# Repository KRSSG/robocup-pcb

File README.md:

# RoboCup PCB Repository

Welcome to the KRRSG's repository for management and storage of RoboCup SSL hardware files! Additional information about the team can be found on the [KRSSG Website](http://www.krssg.in).

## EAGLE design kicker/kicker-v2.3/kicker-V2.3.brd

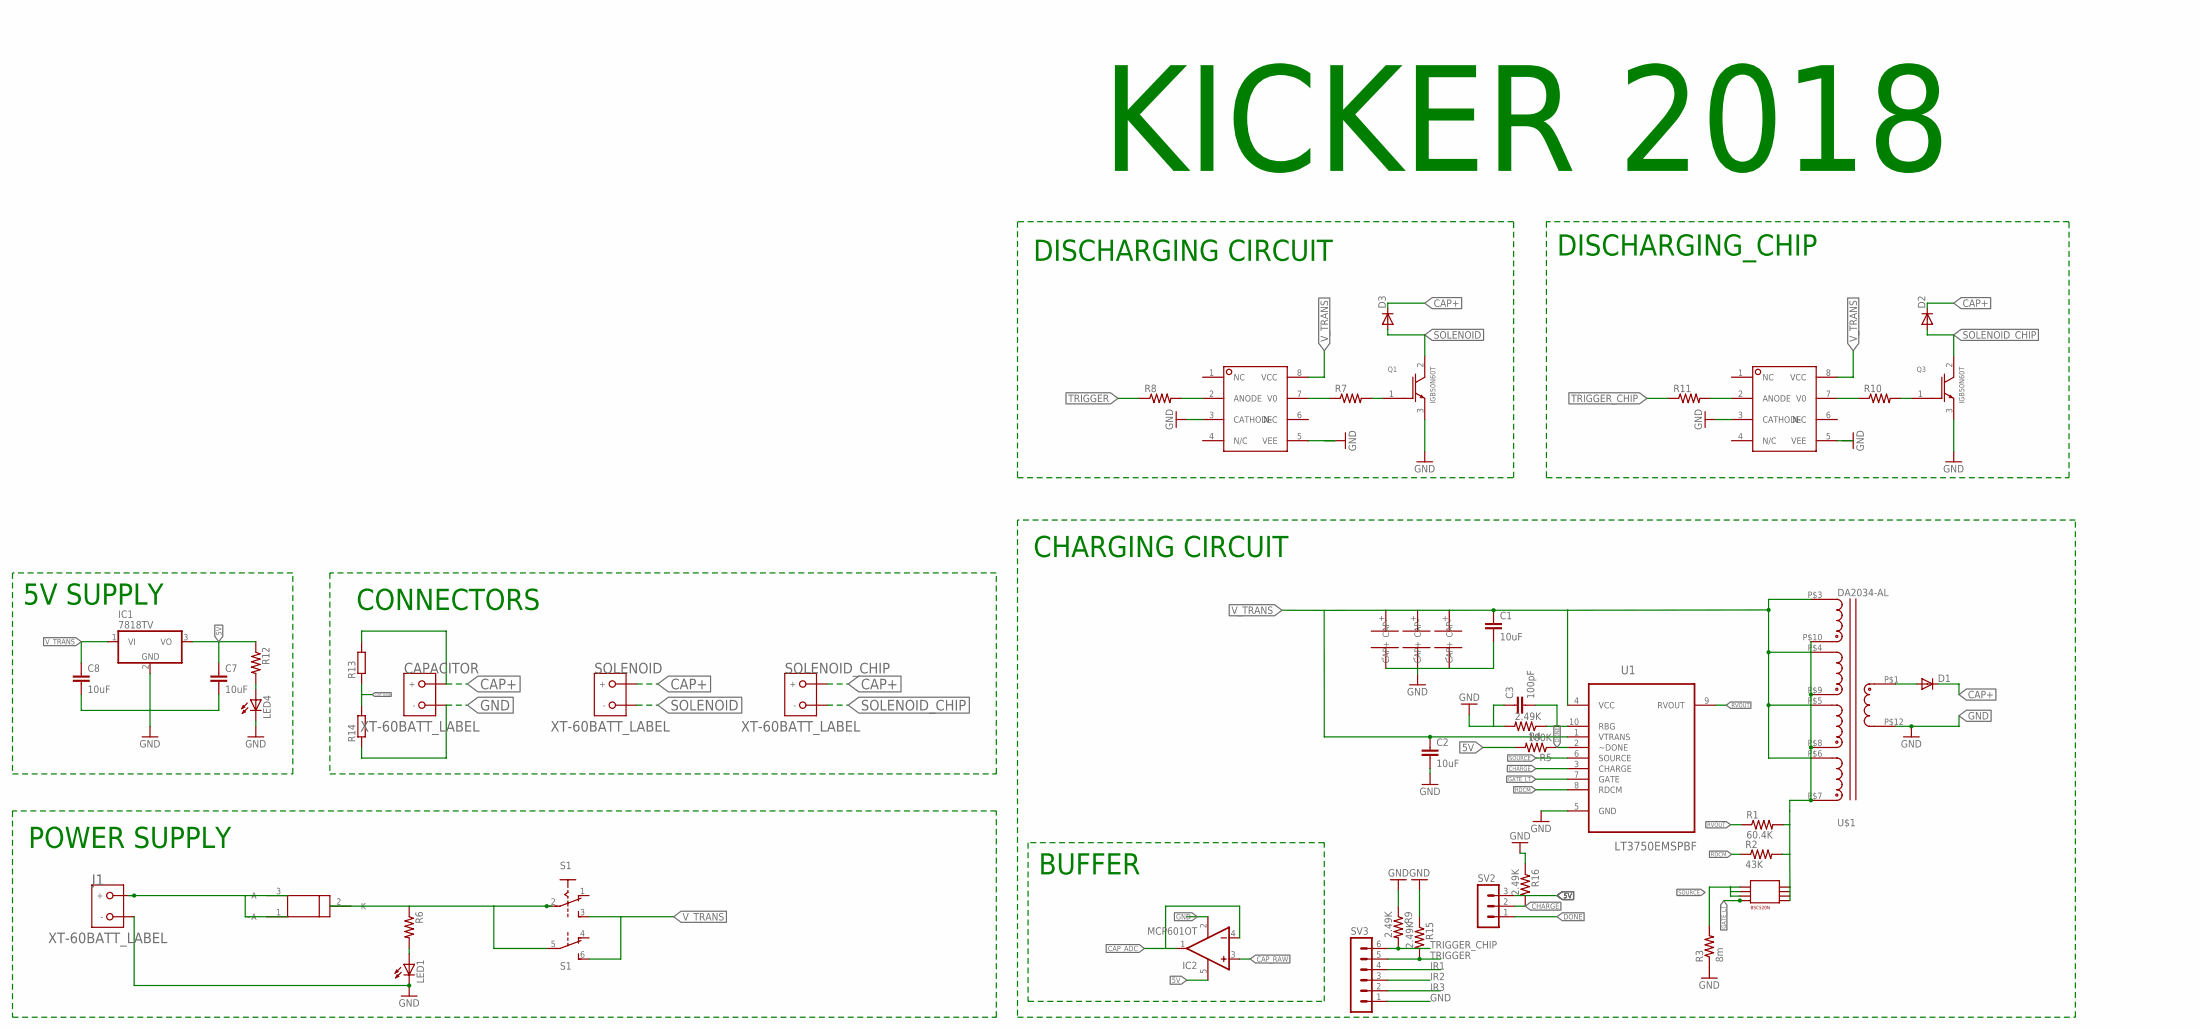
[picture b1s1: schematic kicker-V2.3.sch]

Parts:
C1, C2, C7, C8: 10uF; C1206
C3: 100pF; C1206
CAPACITOR: XT-60BATT_LABEL; XT-60
D1, D2, D3: DIODE-DO214AA; DO214AA
IC1: 7818TV; TO220V
IC2: MCP601OT; SOT23-5
J1: XT-60BATT_LABEL; XT-60
LED1, LED4: LEDCHIPLED_1206; CHIPLED_1206
Q1, Q3: IGB50N60T; TO254P1524X457-3N-2-V
R1: 60.4K; M1206
R2: 43K; M1206
R3: 8m; M1206
R4, R9, R15, R16: 2.49K; M1206
R5: 100K; M1206
R6, R7, R8, R10, R11, R12: R-US_M1206; M1206
R13, R14: R-EU_R0805; R0805
S1: A68-A31
SOLENOID: XT-60BATT_LABEL; XT-60
SOLENOID_CHIP: XT-60BATT_LABEL; XT-60
SV2: MA03-1
SV3: MA06-1
U1: LT3750EMSPBF; SOP50P490X110-10N
U3: LP38690DT-3.3; TO228P1042X238-3N
U$1: DA2034-AL
U$2, U$3, U$4: 56uF; SVP_F12
U$5: BSC520N; PG-TDSON-8
U$6, U$7: HCPL-3120-300E; DIL08

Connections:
5V: C7.1, IC1.3 (VO), IC2.5 (V+), R5.2, R12.1, SV2.3
CAP+: CAPACITOR.BATT (+), D1.C, D2.C, D3.C, R13.2, SOLENOID.BATT (+), SOLENOID_CHIP.BATT (+)
CAP_ADC: IC2.1 (OUT), IC2.4 (-IN)
CAP_RAW: IC2.3 (+IN), R13.1, R14.2
CHARGE: R16.2, SV2.2, U1.3 (CHARGE)
DONE: R5.1, SV2.1, U1.2 (~DONE)
GATE_LT: U1.7 (GATE), U$5.G
GND: C1.2, C2.2, C3.1, C7.2, C8.2, CAPACITOR.GND (-), IC1.2 (GND), IC2.2 (V-), J1.GND (-), LED1.C, LED4.C, Q1.3 (EMITTER), Q3.3 (EMITTER), R3.1, R4.2, R9.1, R14.1, R15.1, R16.1, SV3.1, U1.5 (GND), U$1.P$12 (12), U$2.- (CAP-), U$3.- (CAP-), U$4.- (CAP-), U$6.3 (CATHODE), U$6.5 (VEE), U$7.3 (CATHODE), U$7.5 (VEE)
IR1: SV3.4
IR2: SV3.3
IR3: SV3.2
unnamed: R7.1, U$6.7 (V0)
unnamed: C3.2, R4.1, U1.10 (RBG)
unnamed: R6.1, S1.2, S1.5, U3.2 (K)
unnamed: Q1.1 (GATE), R7.2
unnamed: R8.2, U$6.2 (ANODE)
unnamed: D1.A, U$1.P$1 (1)
unnamed: LED1.A, R6.2
unnamed: R10.1, U$7.7 (V0)
unnamed: Q3.1 (GATE), R10.2
unnamed: R11.2, U$7.2 (ANODE)
unnamed: LED4.A, R12.2
RDCM: R2.1, U1.8 (RDCM)
RVOUT: R1.1, U1.9 (RVOUT)
SINK: R1.2, R2.2, U$1.P$7 (7), U$1.P$8 (8), U$1.P$9 (9), U$1.P$10 (10), U$5.D1, U$5.D2, U$5.D3, U$5.D4
SOLENOID: D3.A, Q1.2 (COLLECTOR), SOLENOID.GND (-)
SOLENOID_CHIP: D2.A, Q3.2 (COLLECTOR), SOLENOID_CHIP.GND (-)
SOURCE: R3.2, U1.6 (SOURCE), U$5.S1, U$5.S2, U$5.S3
TRIGGER: R8.1, R15.2, SV3.5
TRIGGER_CHIP: R9.2, R11.1, SV3.6
VIN: J1.BATT (+), U3.1 (~A), U3.3 (A)
V_TRANS: C1.1, C2.1, C8.1, IC1.1 (VI), S1.3 (S), S1.6 (S), U1.1 (VTRANS), U1.4 (VCC), U$1.P$3 (3), U$1.P$4 (4), U$1.P$5 (5), U$1.P$6 (6), U$2.+ (CAP+), U$3.+ (CAP+), U$4.+ (CAP+), U$6.8 (VCC), U$7.8 (VCC)

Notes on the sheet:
DISCHARGING CIRCUIT
POWER SUPPLY
CHARGING CIRCUIT
DISCHARGING_CHIP
5V SUPPLY
CONNECTORS
KICKER 2018
BUFFER

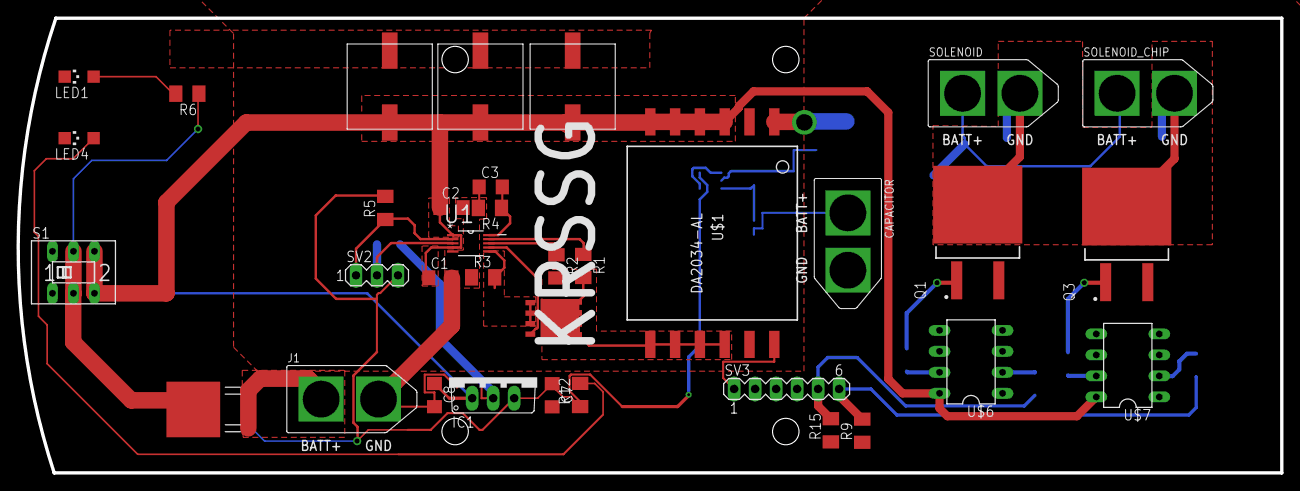
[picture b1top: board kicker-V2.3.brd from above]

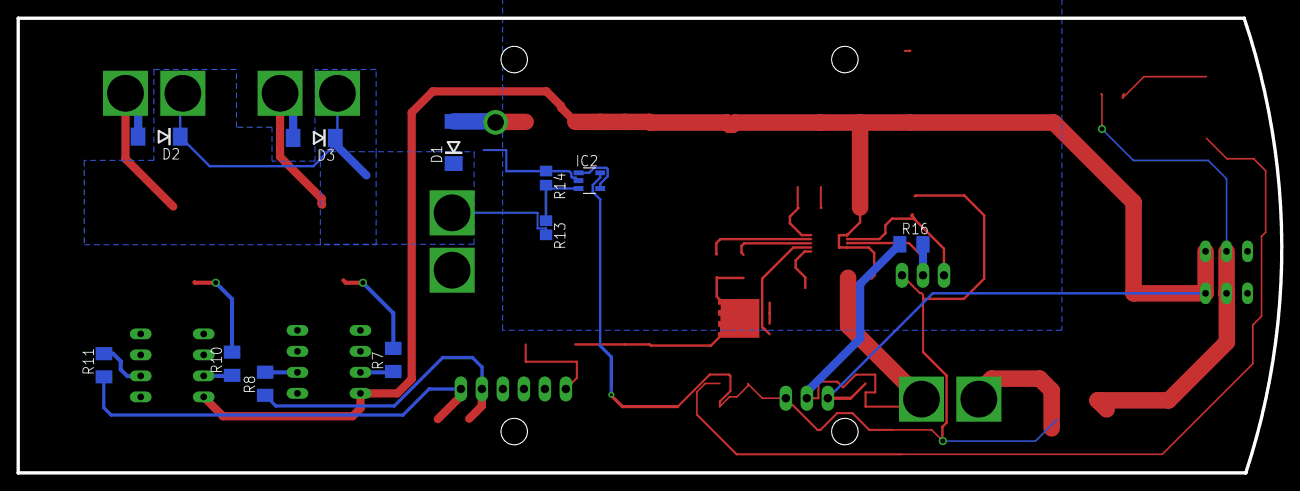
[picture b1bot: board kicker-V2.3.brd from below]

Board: 2 copper layers, 152.9 x 55.0 mm, 46 parts (11 on the bottom side), 29 nets.

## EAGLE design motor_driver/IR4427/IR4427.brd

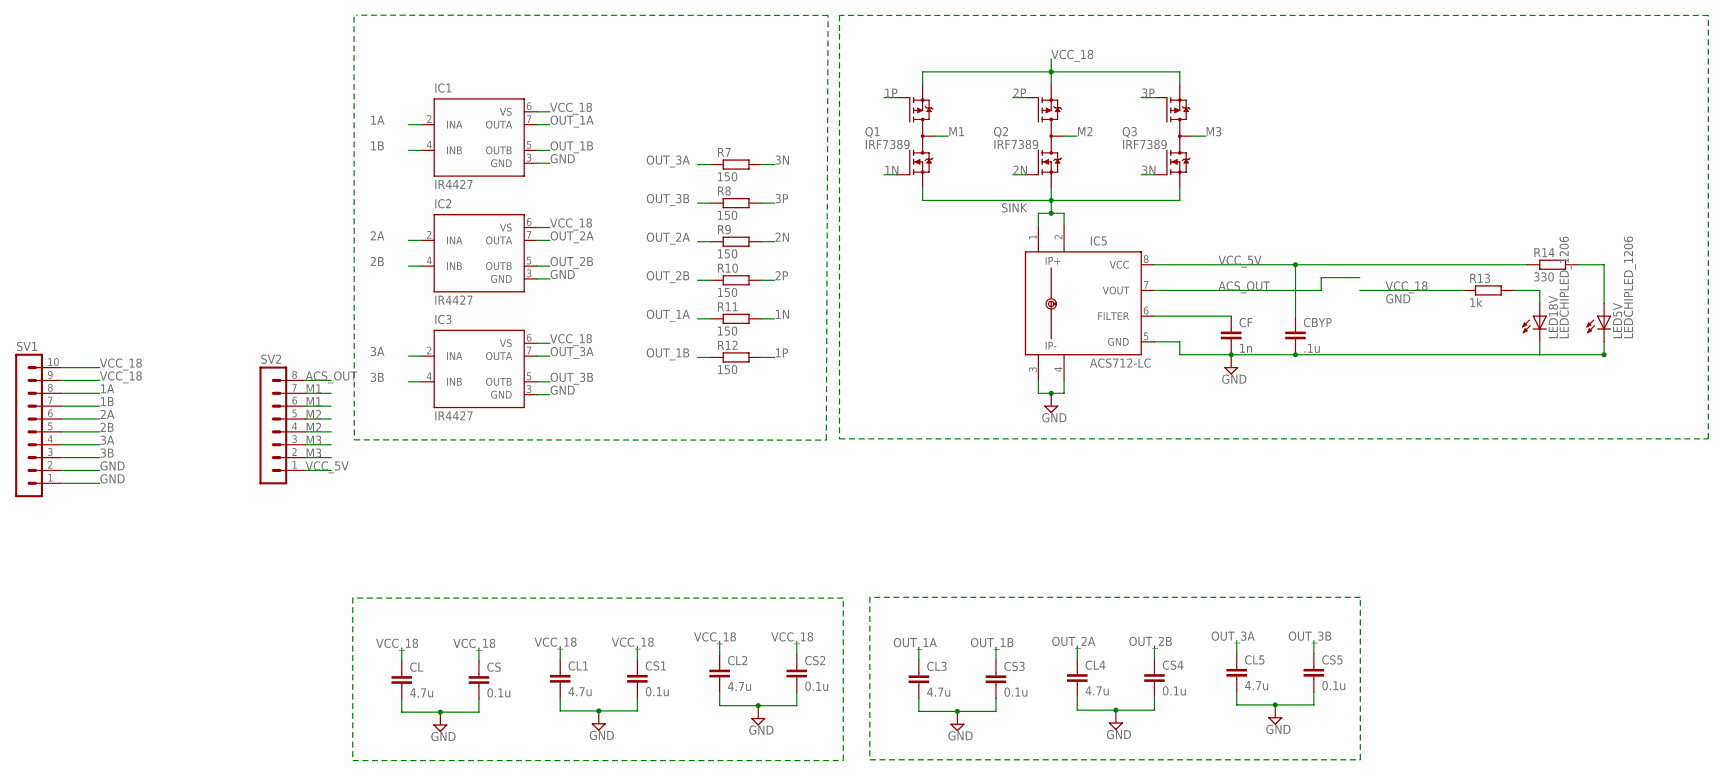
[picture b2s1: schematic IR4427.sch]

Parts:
CBYP: .1u; C1206
CF: 1n; C1206
CL, CL1, CL2, CL3, CL4, CL5: 4.7u; C1206
CS, CS1, CS2, CS3, CS4, CS5: 0.1u; C1206
IC1, IC2, IC3: IR4427; DIL08
IC5: ACS712-LC; SOIC8
LED5V, LED18V: LEDCHIPLED_1206; CHIPLED_1206
Q1, Q2, Q3: IRF7389; SO08-IRF
R7, R8, R9, R10, R11, R12: 150; R1206
R13: 1k; R1206
R14: 330; R1206
SV1: MA10-1
SV2: MA08-1

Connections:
1A: IC1.2 (INA), SV1.8
1B: IC1.4 (INB), SV1.7
1N: Q1.2 (N-G), R11.2
1P: Q1.4 (P-G), R12.2
2A: IC2.2 (INA), SV1.6
2B: IC2.4 (INB), SV1.5
2N: Q2.2 (N-G), R9.2
2P: Q2.4 (P-G), R10.2
3A: IC3.2 (INA), SV1.4
3B: IC3.4 (INB), SV1.3
3N: Q3.2 (N-G), R7.2
3P: Q3.4 (P-G), R8.2
ACS_OUT: IC5.7 (VOUT), SV2.8
GND: CBYP.2, CF.2, CL.2, CL1.2, CL2.2, CL3.2, CL4.2, CL5.2, CS.2, CS1.2, CS2.2, CS3.2, CS4.2, CS5.2, IC1.3 (GND), IC2.3 (GND), IC3.3 (GND), IC5.3 (IP-), IC5.4 (IP-1), IC5.5 (GND), LED5V.C, LED18V.C, SV1.1, SV1.2
M1: Q1.5 (D), Q1.6 (D), Q1.7 (D), Q1.8 (D), SV2.6, SV2.7
M2: Q2.5 (D), Q2.6 (D), Q2.7 (D), Q2.8 (D), SV2.4, SV2.5
M3: Q3.5 (D), Q3.6 (D), Q3.7 (D), Q3.8 (D), SV2.2, SV2.3
unnamed: LED18V.A, R13.2
unnamed: CF.1, IC5.6 (FILTER)
unnamed: LED5V.A, R14.2
OUT_1A: CL3.1, IC1.7 (OUTA), R11.1
OUT_1B: CS3.1, IC1.5 (OUTB), R12.1
OUT_2A: CL4.1, IC2.7 (OUTA), R9.1
OUT_2B: CS4.1, IC2.5 (OUTB), R10.1
OUT_3A: CL5.1, IC3.7 (OUTA), R7.1
OUT_3B: CS5.1, IC3.5 (OUTB), R8.1
SINK: IC5.1 (IP+), IC5.2 (IP+1), Q1.1 (N-S), Q2.1 (N-S), Q3.1 (N-S)
VCC_5V: CBYP.1, IC5.8 (VCC), R14.1, SV2.1
VCC_18: CL.1, CL1.1, CL2.1, CS.1, CS1.1, CS2.1, IC1.6 (VS), IC2.6 (VS), IC3.6 (VS), Q1.3 (P-S), Q2.3 (P-S), Q3.3 (P-S), R13.1, SV1.9, SV1.10

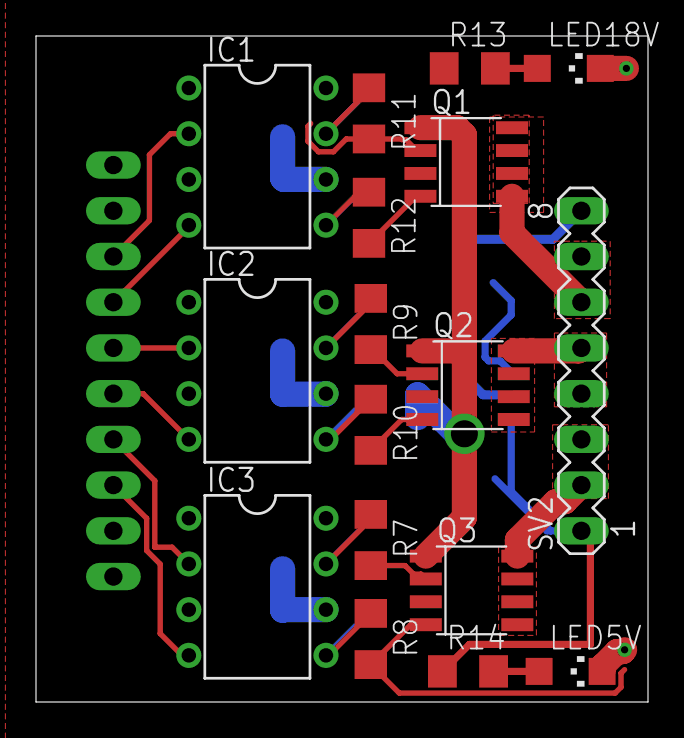
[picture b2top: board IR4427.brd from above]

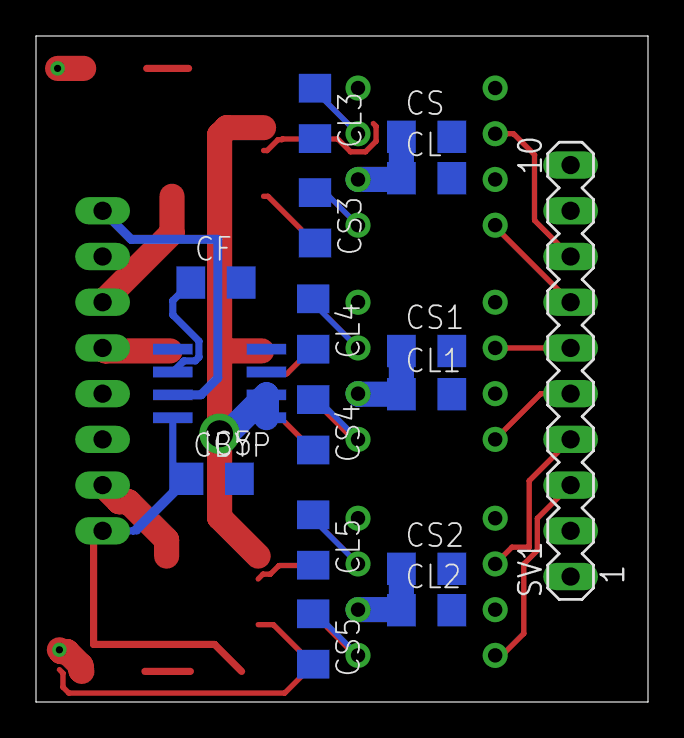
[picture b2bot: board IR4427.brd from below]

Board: 2 copper layers, 34.0 x 37.0 mm, 33 parts (16 on the bottom side), 29 nets.

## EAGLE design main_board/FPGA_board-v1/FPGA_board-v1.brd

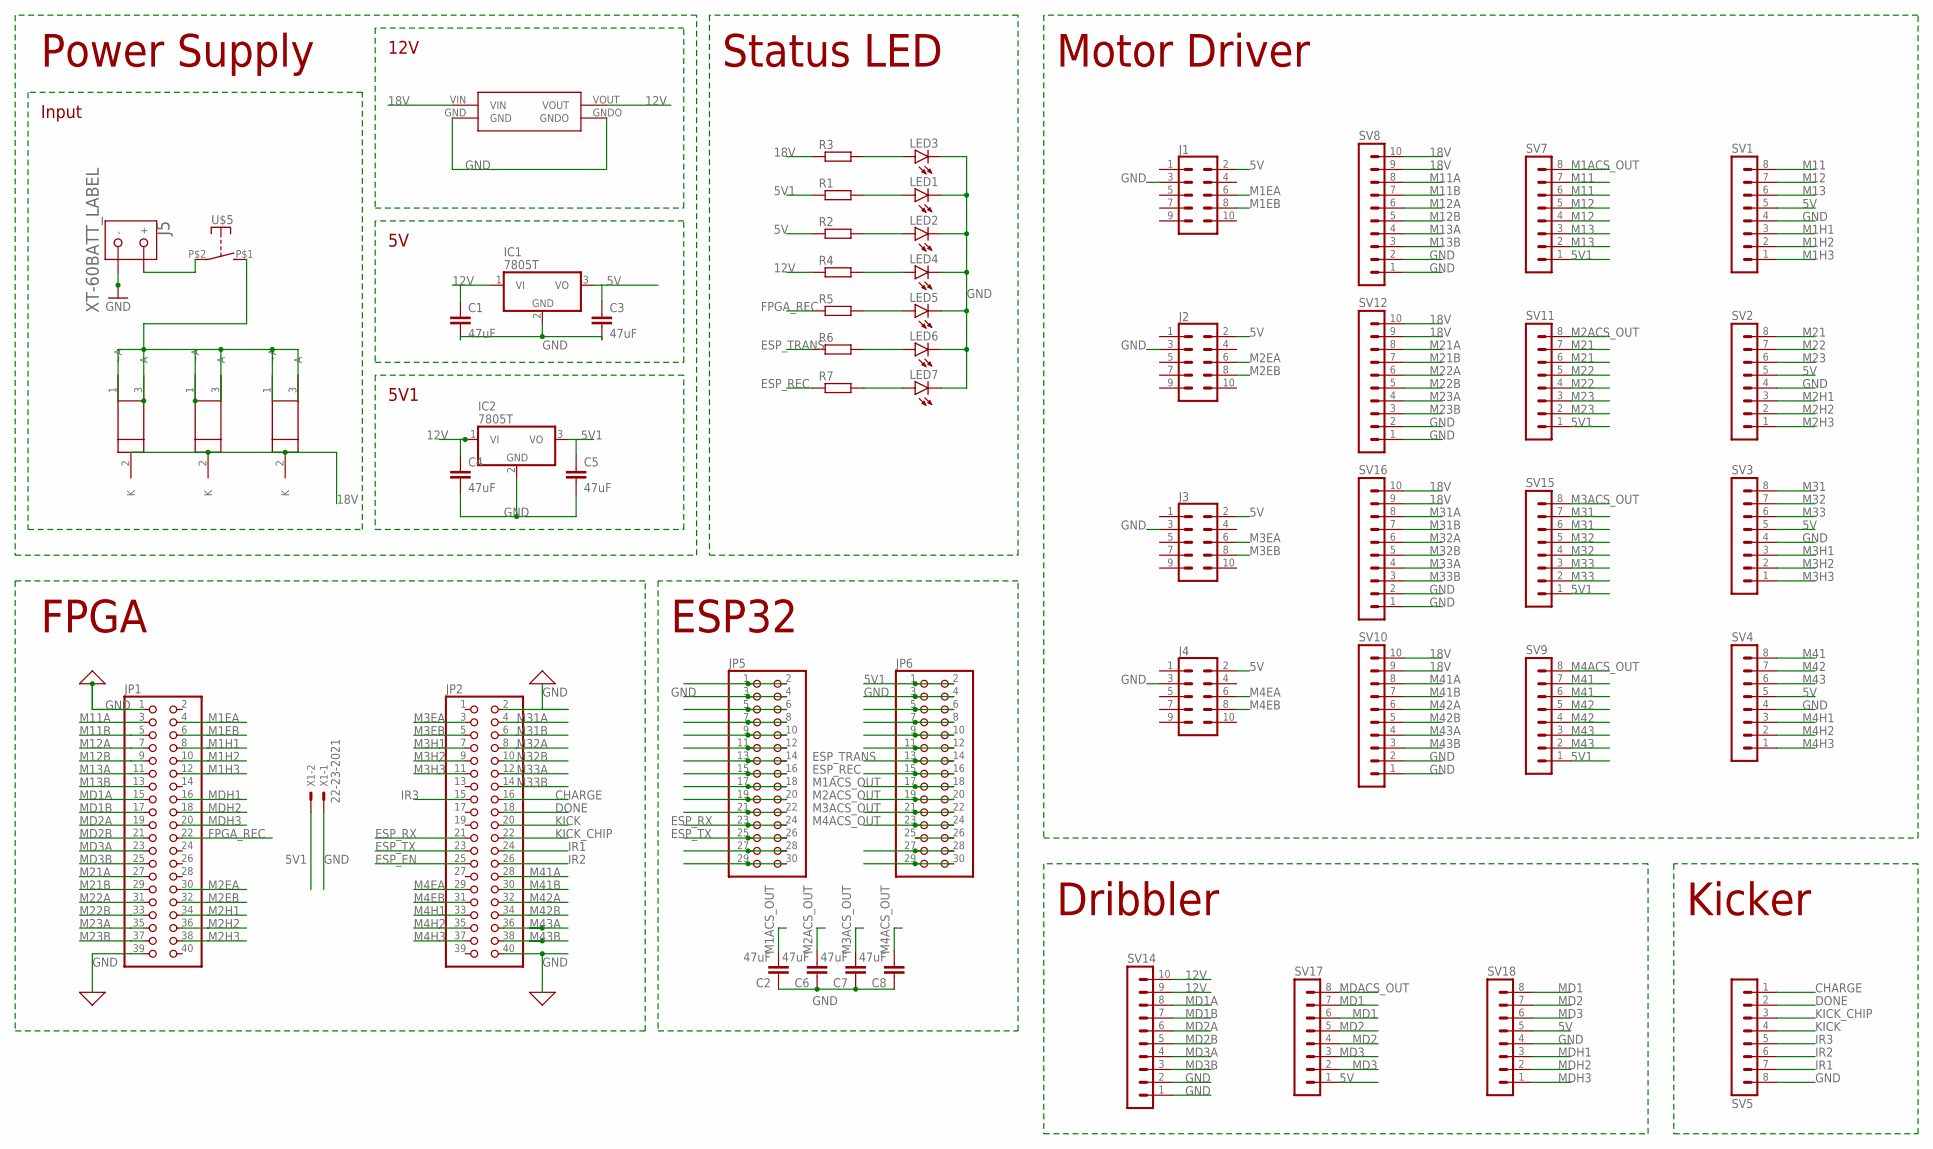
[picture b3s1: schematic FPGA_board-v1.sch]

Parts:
C1, C2, C3, C4, C5, C6, C7, C8: 47uF; C1206
IC1, IC2: 7805T; TO220H
J1, J2, J3, J4: CONN_05X2SHD_LOCK; 2X5-SHROUDED_LOCK
J5: XT-60BATT_LABEL; XT-60
JP1, JP2: PINHD-2X20; 2X20
JP5, JP6: PINHD-2X15; 2X15
LED1, LED2, LED3, LED4, LED5, LED6, LED7: LEDSMT1206; 1206
R1, R2, R3, R4, R5, R6, R7: R-EU_R1206; R1206
SV1, SV2, SV3, SV4, SV5, SV7, SV9, SV11, SV15, SV17, SV18: MA08-1
SV8, SV10, SV12, SV14, SV16: MA10-1
U1, U2, U3: LP38690DT-3.3; TO228P1042X238-3N
U$4: BUCK
U$5: SWITCH_DA10; DA10
X1: 22-23-2021

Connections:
5V: C3.1, IC1.3 (VO), J1.2, J2.2, J3.2, J4.2, R2.1, SV1.5, SV2.5, SV3.5, SV4.5, SV17.1, SV18.5
5V1: C5.1, IC2.3 (VO), JP6.1, JP6.2, R1.1, SV7.1, SV9.1, SV11.1, SV15.1, X1.2
12V: C1.1, C4.1, IC1.1 (VI), IC2.1 (VI), R4.1, SV14.9, SV14.10, U$4.VOUT
18V: R3.1, SV8.9, SV8.10, SV10.9, SV10.10, SV12.9, SV12.10, SV16.9, SV16.10, U1.2 (K), U2.2 (K), U3.2 (K), U$4.VIN
CHARGE: JP2.16, SV5.1
DONE: JP2.18, SV5.2
ESP_EN: JP2.25
ESP_REC: JP6.15, JP6.16, R7.1
ESP_RX: JP2.21, JP5.23, JP5.24
ESP_TRANS: JP6.13, JP6.14, R6.1
ESP_TX: JP2.23, JP5.25, JP5.26
FPGA_REC: JP1.22, R5.1
GND: C1.2, C2.1, C3.2, C4.2, C5.2, C6.1, C7.1, C8.1, IC1.2 (GND), IC2.2 (GND), J1.3, J2.3, J3.3, J4.3, J5.GND (-), JP1.1, JP1.39, JP2.2, JP2.40, JP5.3, JP5.4, JP6.3, JP6.4, LED1.C, LED2.C, LED3.C, LED4.C, LED5.C, LED6.C, LED7.C, SV1.4, SV2.4, SV3.4, SV4.4, SV5.8, SV8.1, SV8.2, SV10.1, SV10.2, SV12.1, SV12.2, SV14.1, SV14.2, SV16.1, SV16.2, SV18.4, U$4.GND, U$4.GNDO, X1.1
INPUT: U1.1 (~A), U1.3 (A), U2.1 (~A), U2.3 (A), U3.1 (~A), U3.3 (A), U$5.P$1 (S)
IR1: JP2.24, SV5.7
IR2: JP2.26, SV5.6
IR3: JP2.15, SV5.5
KICK: JP2.20, SV5.4
KICK_CHIP: JP2.22, SV5.3
M1ACS_OUT: C2.2, JP6.17, JP6.18, SV7.8
M1EA: J1.6, JP1.4
M1EB: J1.8, JP1.6
M1H1: JP1.8, SV1.3
M1H2: JP1.10, SV1.2
M1H3: JP1.12, SV1.1
M2ACS_OUT: C6.2, JP6.19, JP6.20, SV11.8
M2EA: J2.6, JP1.30
M2EB: J2.8, JP1.32
M2H1: JP1.34, SV2.3
M2H2: JP1.36, SV2.2
M2H3: JP1.38, SV2.1
M3ACS_OUT: C7.2, JP6.21, JP6.22, SV15.8
M3EA: J3.6, JP2.3
M3EB: J3.8, JP2.5
M3H1: JP2.7, SV3.3
M3H2: JP2.9, SV3.2
M3H3: JP2.11, SV3.1
M4ACS_OUT: C8.2, JP6.23, JP6.24, SV9.8
M4EA: J4.6, JP2.29
M4EB: J4.8, JP2.31
M4H1: JP2.33, SV4.3
M4H2: JP2.35, SV4.2
M4H3: JP2.37, SV4.1
M11: SV1.8, SV7.6, SV7.7
M11A: JP1.3, SV8.8
M11B: JP1.5, SV8.7
M12: SV1.7, SV7.4, SV7.5
M12A: JP1.7, SV8.6
M12B: JP1.9, SV8.5
M13: SV1.6, SV7.2, SV7.3
M13A: JP1.11, SV8.4
M13B: JP1.13, SV8.3
M21: SV2.8, SV11.6, SV11.7
M21A: JP1.27, SV12.8
M21B: JP1.29, SV12.7
M22: SV2.7, SV11.4, SV11.5
M22A: JP1.31, SV12.6
M22B: JP1.33, SV12.5
M23: SV2.6, SV11.2, SV11.3
M23A: JP1.35, SV12.4
M23B: JP1.37, SV12.3
M31: SV3.8, SV15.6, SV15.7
M31A: JP2.4, SV16.8
M31B: JP2.6, SV16.7
M32: SV3.7, SV15.4, SV15.5
M32A: JP2.8, SV16.6
M32B: JP2.10, SV16.5
M33: SV3.6, SV15.2, SV15.3
M33A: JP2.12, SV16.4
M33B: JP2.14, SV16.3
M41: SV4.8, SV9.6, SV9.7
M41A: JP2.28, SV10.8
M41B: JP2.30, SV10.7
M42: SV4.7, SV9.4, SV9.5
M42A: JP2.32, SV10.6
M42B: JP2.34, SV10.5
M43: SV4.6, SV9.2, SV9.3
M43A: JP2.36, SV10.4
M43B: JP2.38, SV10.3
MD1: SV17.6, SV17.7, SV18.8
MD1A: JP1.15, SV14.8
MD1B: JP1.17, SV14.7
MD2: SV17.4, SV17.5, SV18.7
MD2A: JP1.19, SV14.6
MD2B: JP1.21, SV14.5
MD3: SV17.2, SV17.3, SV18.6
MD3A: JP1.23, SV14.4
MD3B: JP1.25, SV14.3
MDACS_OUT: SV17.8
MDH1: JP1.16, SV18.3
MDH2: JP1.18, SV18.2
MDH3: JP1.20, SV18.1
unnamed: JP5.1, JP5.2
unnamed: LED1.A, R1.2
unnamed: JP5.5, JP5.6
unnamed: LED2.A, R2.2
unnamed: JP5.7, JP5.8
unnamed: JP5.9, JP5.10
unnamed: LED3.A, R3.2
unnamed: JP5.11, JP5.12
unnamed: JP5.13, JP5.14
unnamed: LED4.A, R4.2
unnamed: JP5.15, JP5.16
unnamed: JP5.17, JP5.18
unnamed: LED5.A, R5.2
unnamed: JP5.19, JP5.20
unnamed: JP5.21, JP5.22
unnamed: LED6.A, R6.2
unnamed: LED7.A, R7.2
unnamed: JP5.27, JP5.28
unnamed: JP5.29, JP5.30
unnamed: JP6.5, JP6.6
unnamed: JP6.7, JP6.8
unnamed: JP6.9, JP6.10
unnamed: JP6.11, JP6.12
unnamed: JP6.27, JP6.28
unnamed: JP6.29, JP6.30
unnamed: JP6.25, JP6.26
SUPP: J5.BATT (+), U$5.P$2

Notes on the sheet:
Power Supply
FPGA
Status LED
Motor Driver
Dribbler
Kicker
ESP32
Input
12V
5V1

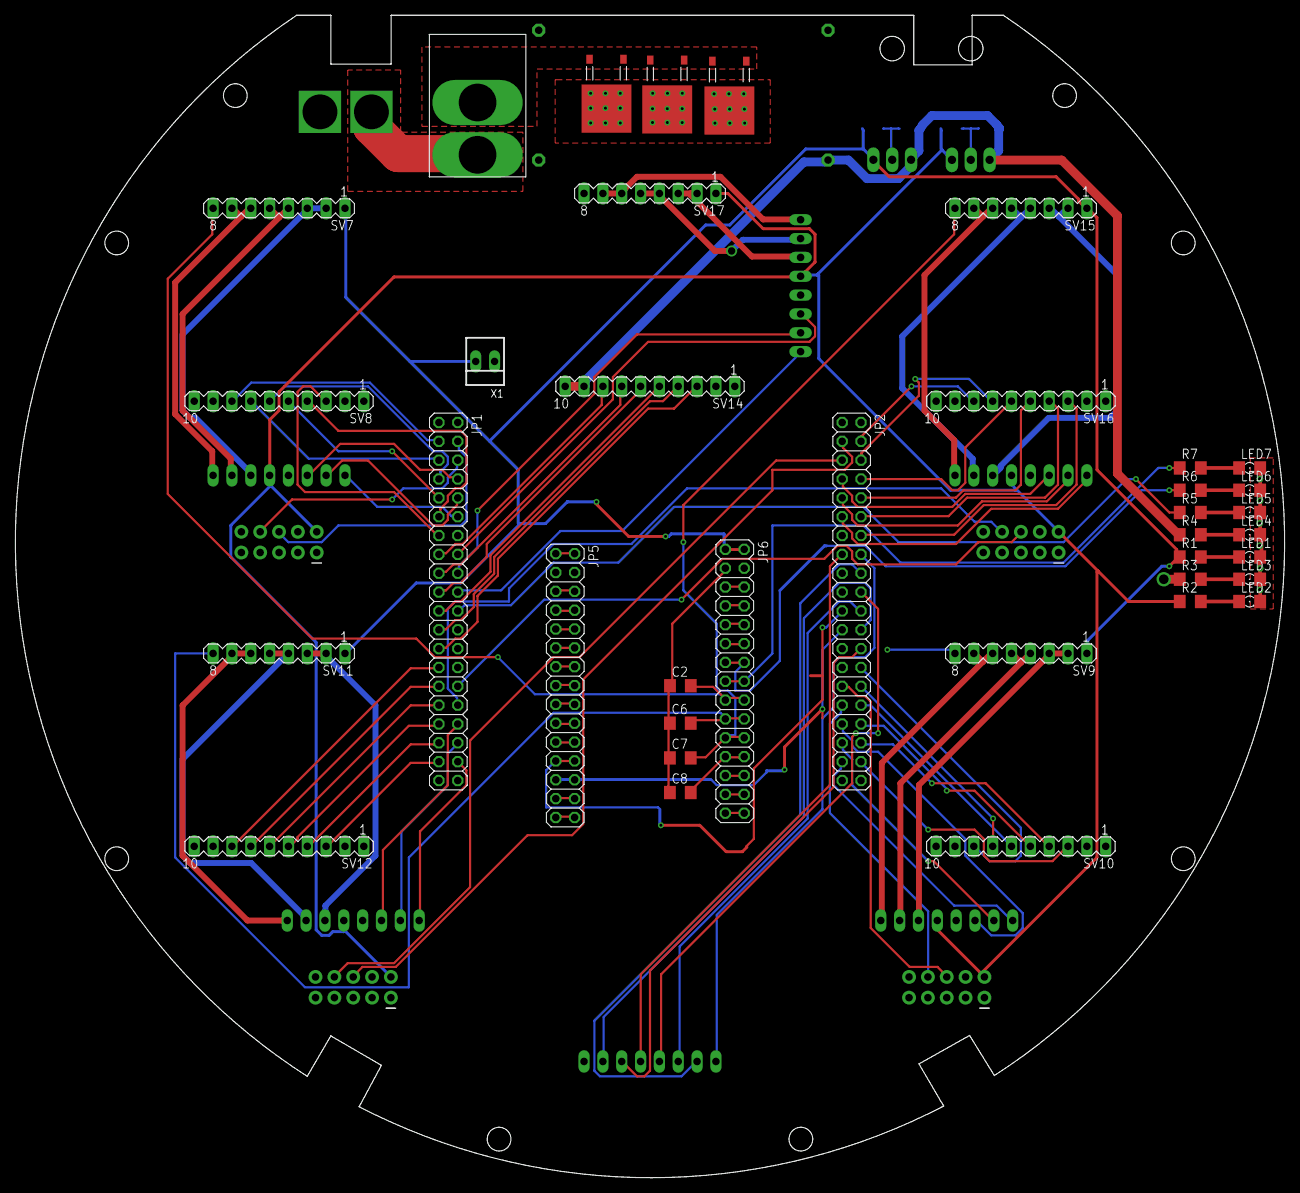
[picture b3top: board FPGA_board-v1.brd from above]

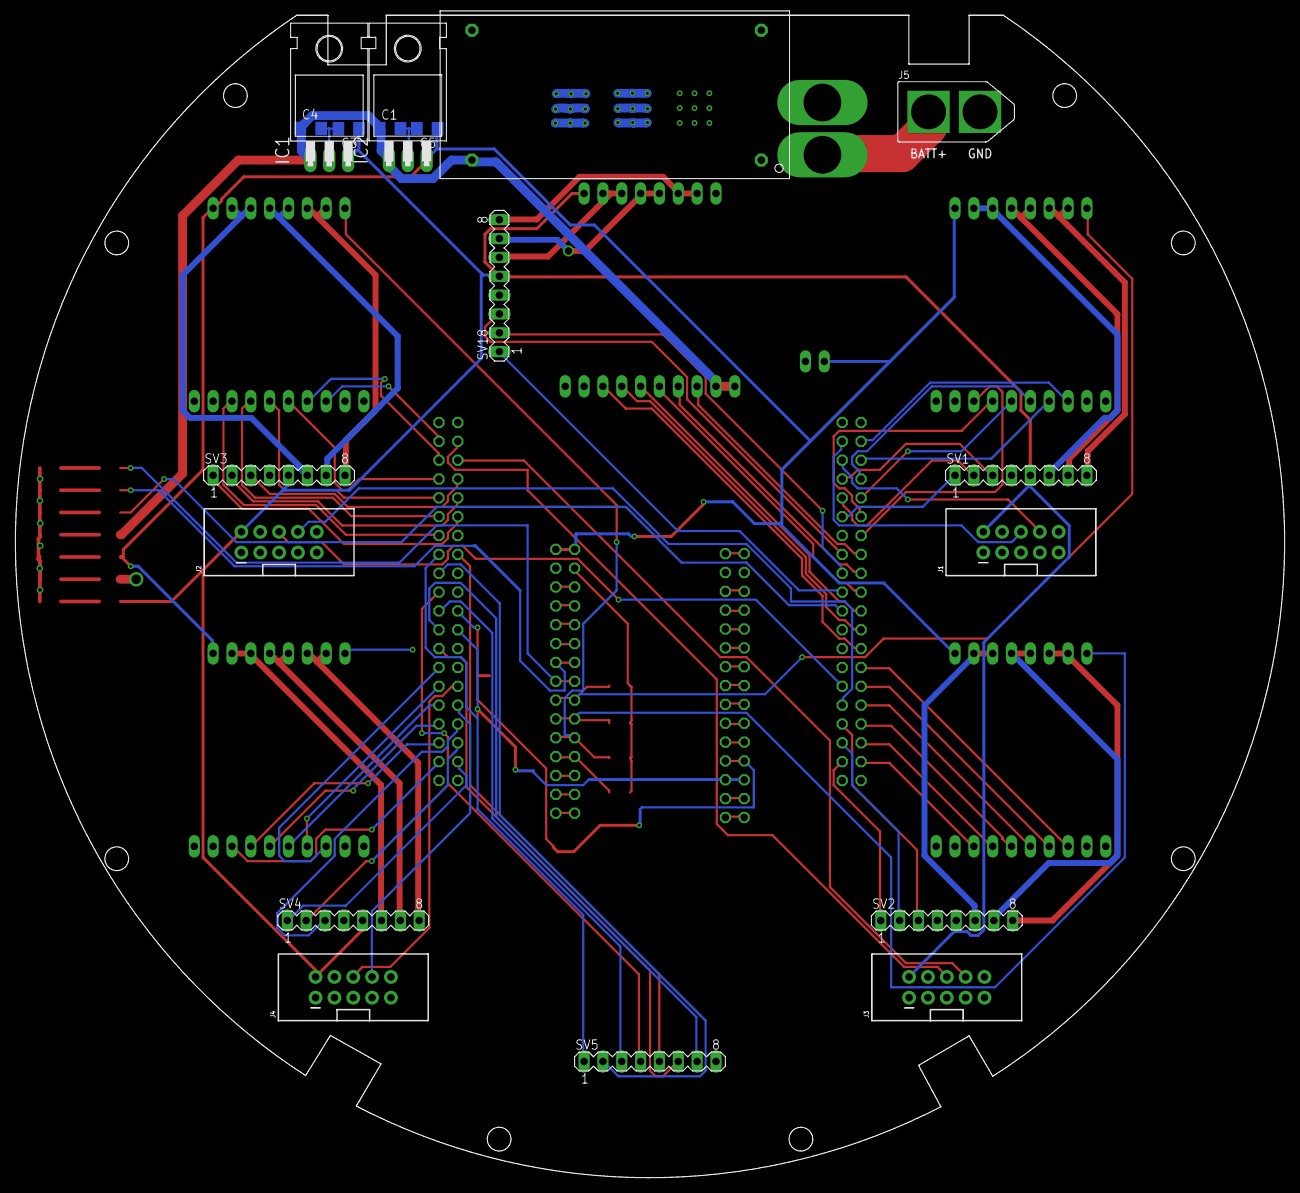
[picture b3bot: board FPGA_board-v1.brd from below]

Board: 4 copper layers, 171.1 x 156.7 mm, 55 parts (18 on the bottom side), 117 nets.

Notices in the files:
parts and their libraries:
SparkFun-Connectors: Licensing: Creative Commons ShareAlike 4.0 International - https://creativecommons.org/licenses/by-sa/4.0
STM32F407Vx_LQFP100: Copyright 2012 by Ersan Günes, Quantitec, info@quantitec.de
con-headers-jp: Copyright (C) 2008, Bob Starr
